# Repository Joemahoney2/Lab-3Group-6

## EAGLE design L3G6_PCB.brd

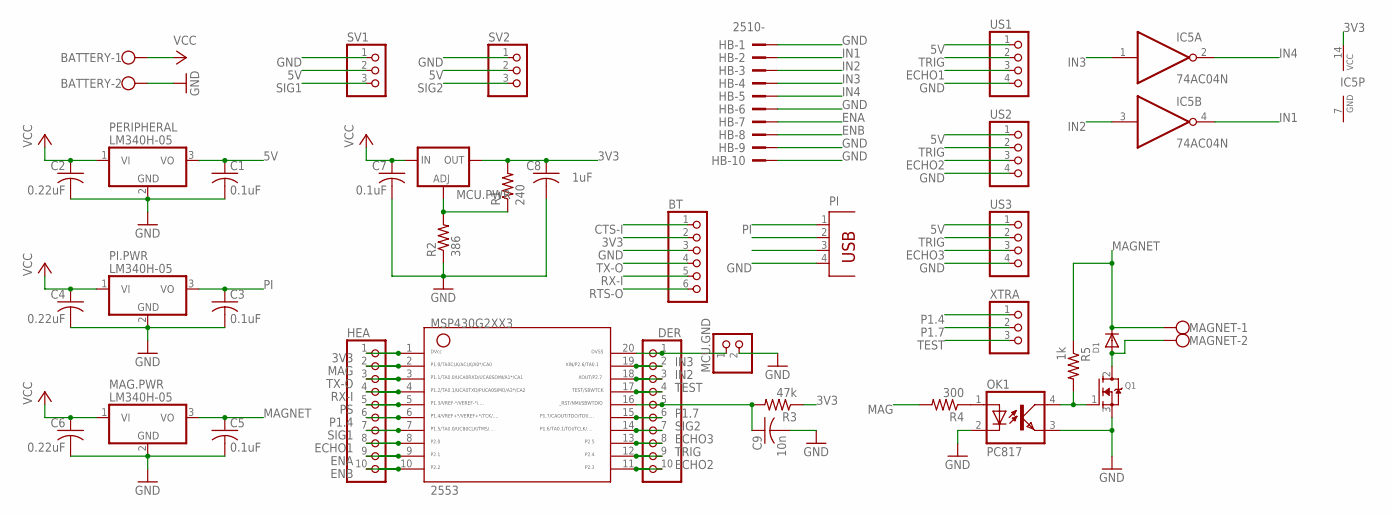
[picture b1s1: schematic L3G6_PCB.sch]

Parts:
2553: G2XX3---N20; N20
BATTERY: W237-102
BT: PINHD-1X6; 1X06
C1, C3, C5, C7: 0.1uF; C050-025X075
C2, C4, C6: 0.22uF; C050-025X075
C8: 1uF; C050-025X075
C9: 10n; C050-025X075
D1: DIODEDO-1N4148; DO-1N4148
DER: PINHD-1X10; 1X10
HB: 2510-; PAK100/2500-10
HEA: PINHD-1X10; 1X10
IC5: 74AC04N; DIL14
MAG.PWR: LM340H-05; TO220H
MAGNET: W237-102
MCU.GND: PINHD-1X2; 1X02
MCU.PWR: LM317TS; 317TS
OK1: PC817; DIL04
PERIPHERAL: LM340H-05; TO220H
PI: PN87520
PI.PWR: LM340H-05; TO220H
Q1: MOSFET-NGDS_TO220V; TO220V
R1: 240; 0207/10
R2: 386; 0207/10
R3: 47k; 0207/10
R4: 300; 0207/10
R5: 1k; 0207/10
SV1, SV2: PINHD-1X3; 1X03
US1, US2, US3: PINHD-1X4; 1X04
XTRA: PINHD-1X3; 1X03

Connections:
3V3: 2553.1, BT.2, C8.1, HEA.1, IC5.14 (VCC), MCU.PWR.2 (OUT), R1.2, R3.1
5V: C1.1, PERIPHERAL.3 (VO), SV1.2, SV2.2, US1.1, US2.1, US3.1
CTS-I: BT.1
ECHO1: 2553.8, HEA.8, US1.3
ECHO2: 2553.11, DER.10, US2.3
ECHO3: 2553.13, DER.8, US3.3
ENA: 2553.9, HB.7, HEA.9
ENB: 2553.10, HB.8, HEA.10
GND: BATTERY.2, BT.3, C1.2, C2.2, C3.2, C4.2, C5.2, C6.2, C7.2, C8.2, C9.2, HB.1, HB.6, HB.9, HB.10, IC5.7 (GND), MAG.PWR.2 (GND), MCU.GND.2, OK1.2 (C), OK1.3 (EMIT), PERIPHERAL.2 (GND), PI.4, PI.PWR.2 (GND), Q1.3 (S), R2.1, SV1.1, SV2.1, US1.4, US2.4, US3.4
IN1: HB.2, IC5.4 (O)
IN2: 2553.18, DER.3, HB.3, IC5.3 (I)
IN3: 2553.19, DER.2, HB.4, IC5.1 (I)
IN4: HB.5, IC5.2 (O)
MAG: 2553.2, HEA.2, R4.2
MAGNET: C5.1, D1.C, MAG.PWR.3 (VO), MAGNET.1, R5.1
unnamed: 2553.16, C9.1, DER.5, R3.2
unnamed: MCU.PWR.1 (ADJ), R1.1, R2.2
unnamed: OK1.1 (A), R4.1
unnamed: 2553.20, DER.1, MCU.GND.1
unnamed: D1.A, MAGNET.2, Q1.2 (D)
unnamed: OK1.4 (COL), Q1.1 (G), R5.2
P1.4: 2553.6, HEA.6, XTRA.1
P1.7: 2553.15, DER.6, XTRA.2
PI: C3.1, PI.1, PI.PWR.3 (VO)
PS: 2553.5, HEA.5
RTS-O: BT.6
RX-I: 2553.4, BT.5, HEA.4
SIG1: 2553.7, HEA.7, SV1.3
SIG2: 2553.14, DER.7, SV2.3
TEST: 2553.17, DER.4, XTRA.3
TRIG: 2553.12, DER.9, US1.2, US2.2, US3.2
TX-O: 2553.3, BT.4, HEA.3
VCC: BATTERY.1, C2.1, C4.1, C6.1, C7.1, MAG.PWR.1 (VI), MCU.PWR.3 (IN), PERIPHERAL.1 (VI), PI.PWR.1 (VI)

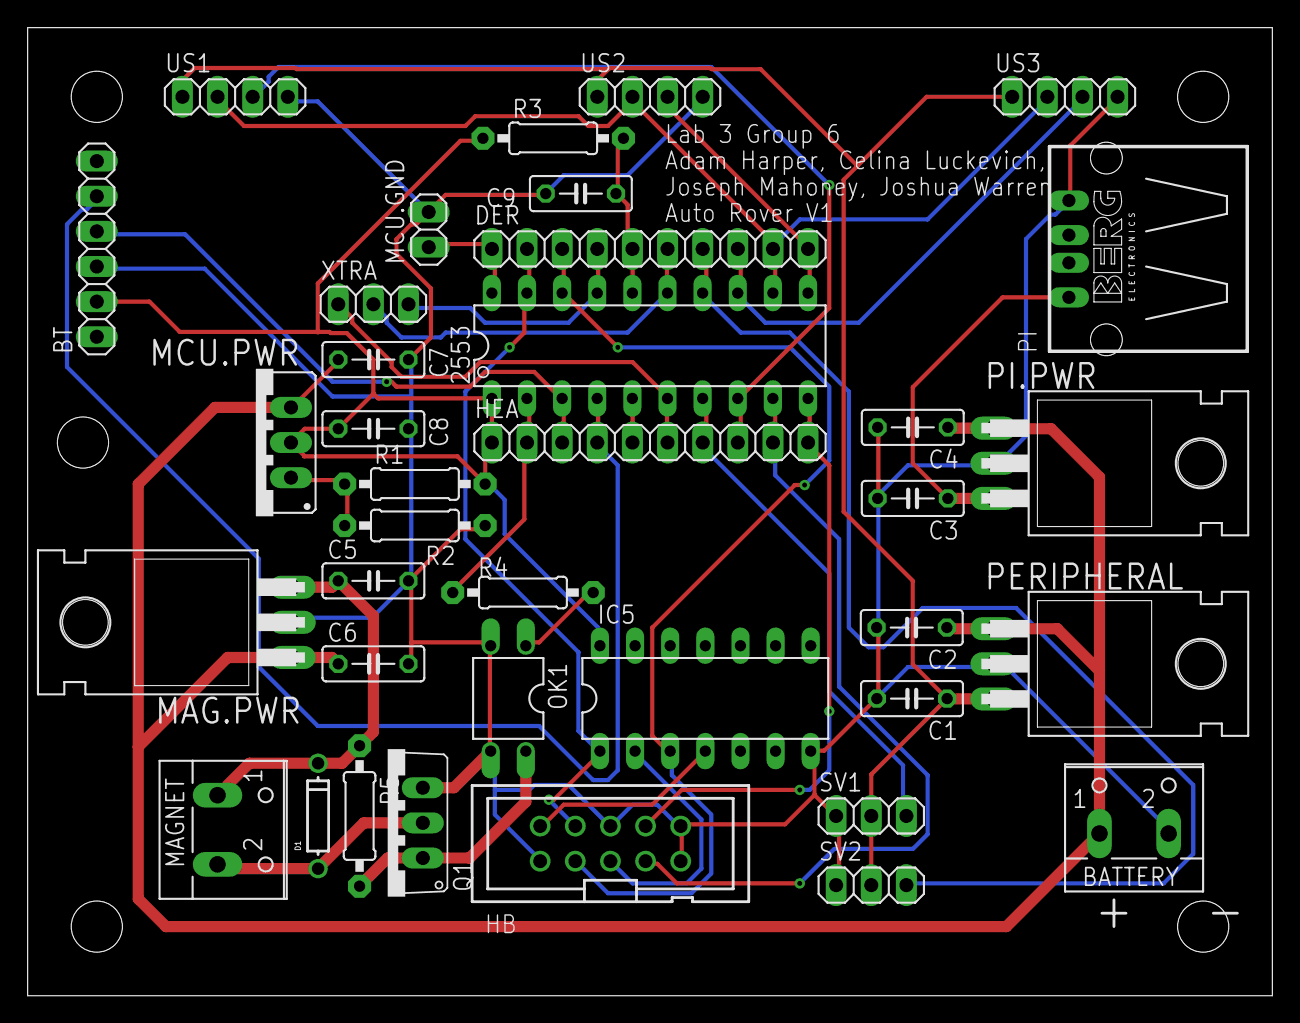
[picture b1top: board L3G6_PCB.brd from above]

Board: 2 copper layers, 90.0 x 70.0 mm, 37 parts (0 on the bottom side), 31 nets.

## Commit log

2018-10-09 Create Data Sheets
2018-10-10 Update Data Sheets
2018-10-15 Integrated with Top to drive rover via bluetooth
2018-10-15 Integrated with GUI to control rover via bluetooth
2018-10-15 Gantt Chart
2018-10-15 GUI Template
2018-10-16 Object Tracing
    Full code for best object tracking
2018-10-16 Basic filter and stream
2018-10-16 AutoCAD designs
2018-10-17 Current Rover Command Code
    For use on the MSP430G2553
2018-10-18 Tentative Top and GUI modules
2018-10-24 Create Servo control
2018-10-24 Update Servo control
2018-10-28 Code for object tracking with direction commands
2018-10-28 Object Detection and Instruction Derivation
2018-10-29 GUI and driving using Object Detection (maybe latency issues)
2018-11-12 MSP code 11-12-2018
2018-11-12 MSP code - WORKING with arm - 11-12-2018
2018-11-14 Computer code: 11-13-18
2018-11-16 Rover PCB Files
    PCB EAGLE files. 11/15/2018
2018-11-16 MSP code 11-16-18 (Pressure Sensors working)
2018-11-19 MCU Code 11/19/18
2018-11-21 Create No Flag Seen obj.detect. code
2018-11-27 Streamlined Object Detection code
2018-11-28 11/27/2018
2018-11-30 11-29-18
2018-11-30 11/29/18
2018-12-01 Final Python Code
2018-12-01 Final MSP code
